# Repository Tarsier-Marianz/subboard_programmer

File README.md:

A simple prototyping board for sub-board programmer extender.

### Thanks

[KiCad IDE](http://kicad-pcb.org/) - for letting me use a free software in designing PCB

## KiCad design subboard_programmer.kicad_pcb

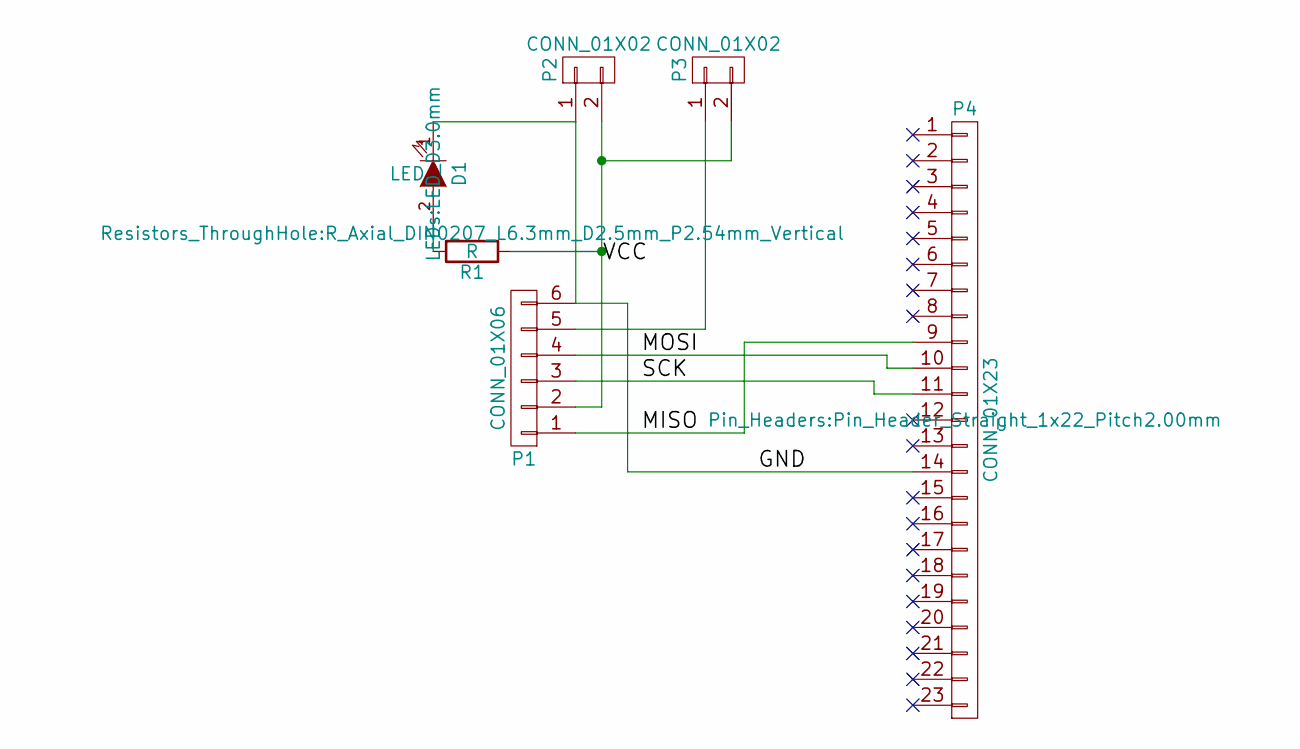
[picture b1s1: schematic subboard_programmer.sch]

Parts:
D1: LED; LED_D3.0mm
P1: CONN_01X06; Pin_Header_Straight_2x03_Pitch2.54mm
P2, P3: CONN_01X02; SDL-102-X-XX_2x01
P4: CONN_01X23; Pin_Header_Straight_1x22_Pitch2.00mm
R1: R; R_Axial_DIN0207_L6.3mm_D2.5mm_P2.54mm_Vertical

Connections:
/GND: D1.1 (K), P1.6, P2.1, P4.14
/MISO: P1.1, P4.9
/MOSI: P1.4, P4.10
/SCK: P1.3, P4.11
/VCC: P1.2, P2.2, P3.2, R1.1
unnamed: D1.2 (A), R1.2
unnamed: P1.5, P3.1

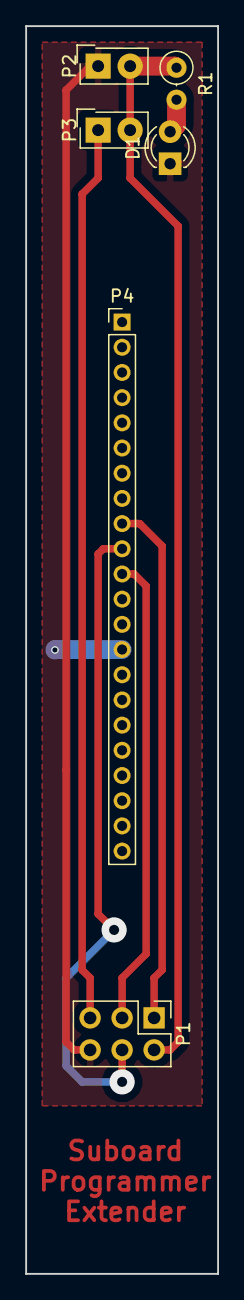
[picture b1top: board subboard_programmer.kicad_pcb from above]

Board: 2 copper layers, 15.2 x 99.1 mm, 6 parts (0 on the bottom side), 7 nets.

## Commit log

2018-02-28 Add readme
